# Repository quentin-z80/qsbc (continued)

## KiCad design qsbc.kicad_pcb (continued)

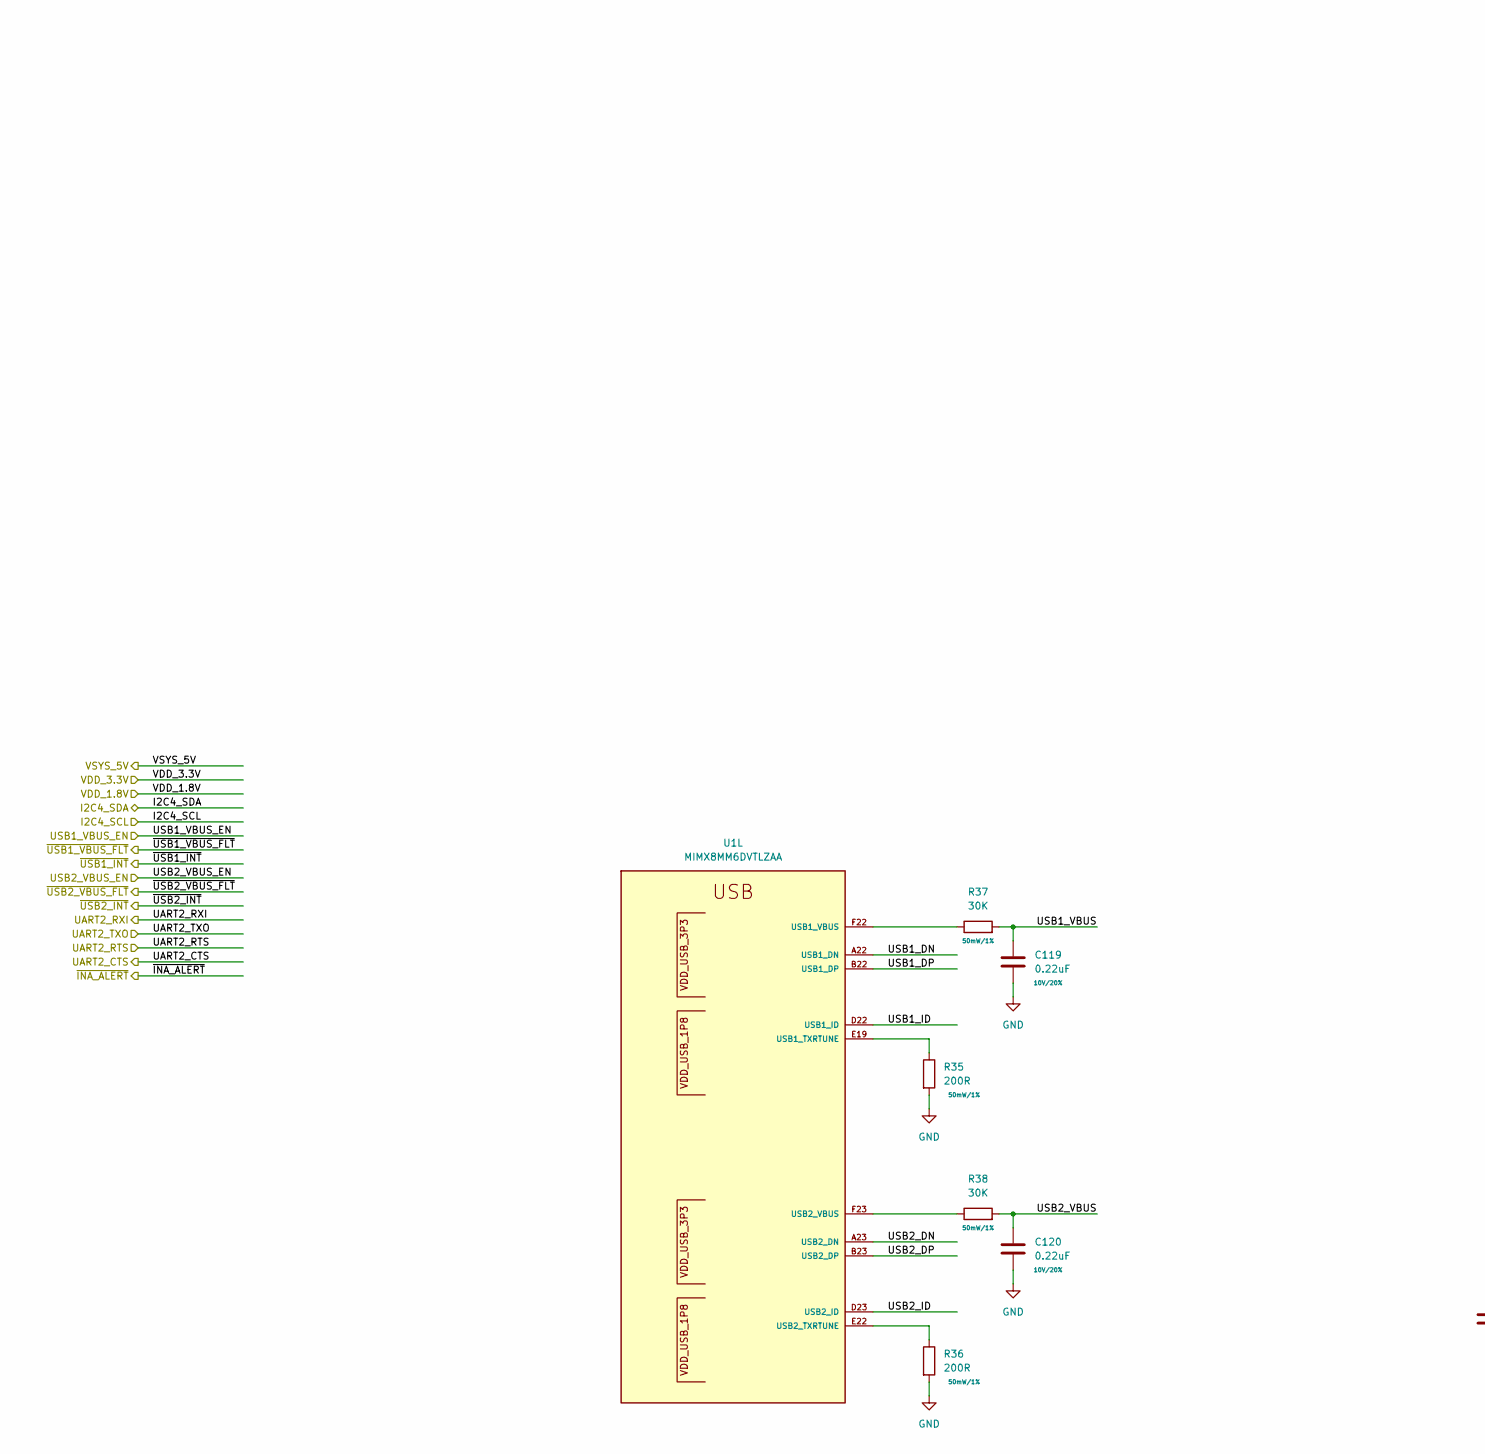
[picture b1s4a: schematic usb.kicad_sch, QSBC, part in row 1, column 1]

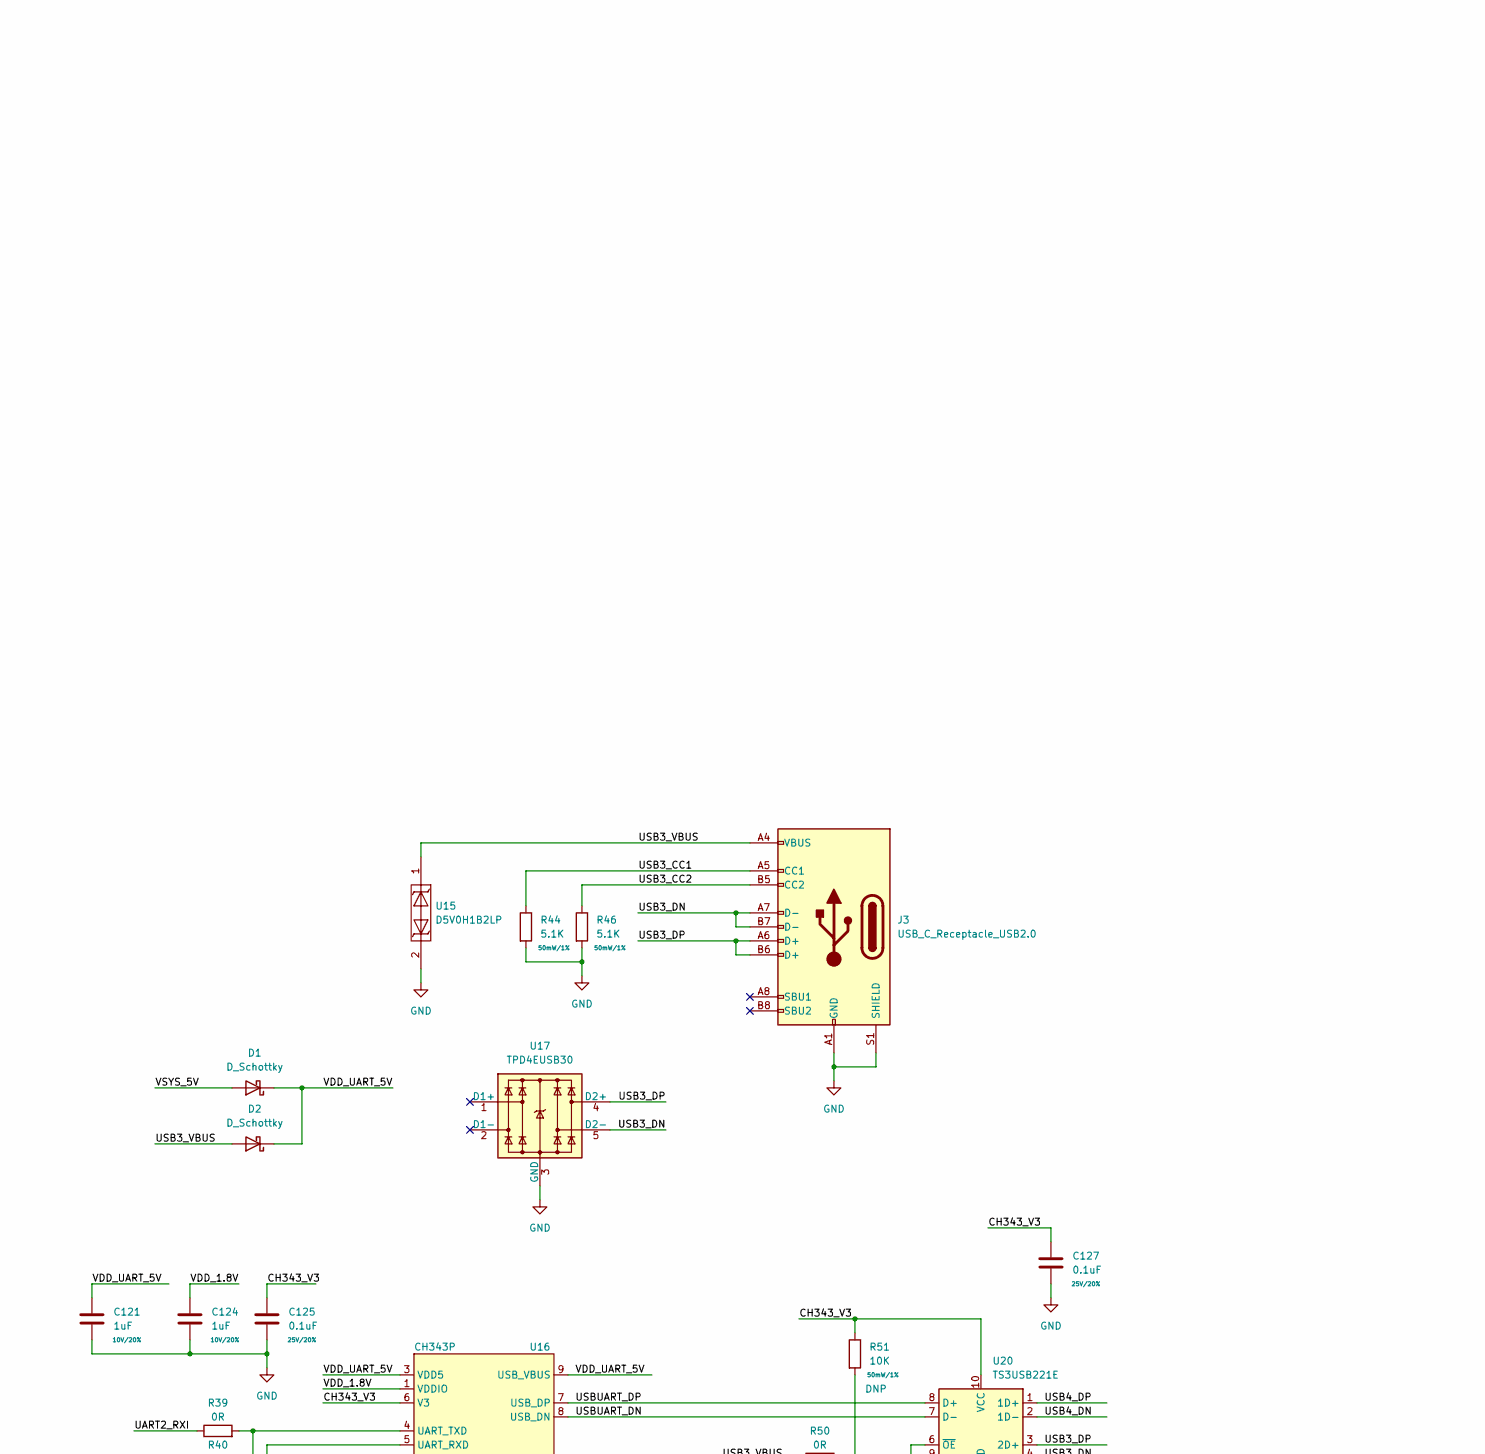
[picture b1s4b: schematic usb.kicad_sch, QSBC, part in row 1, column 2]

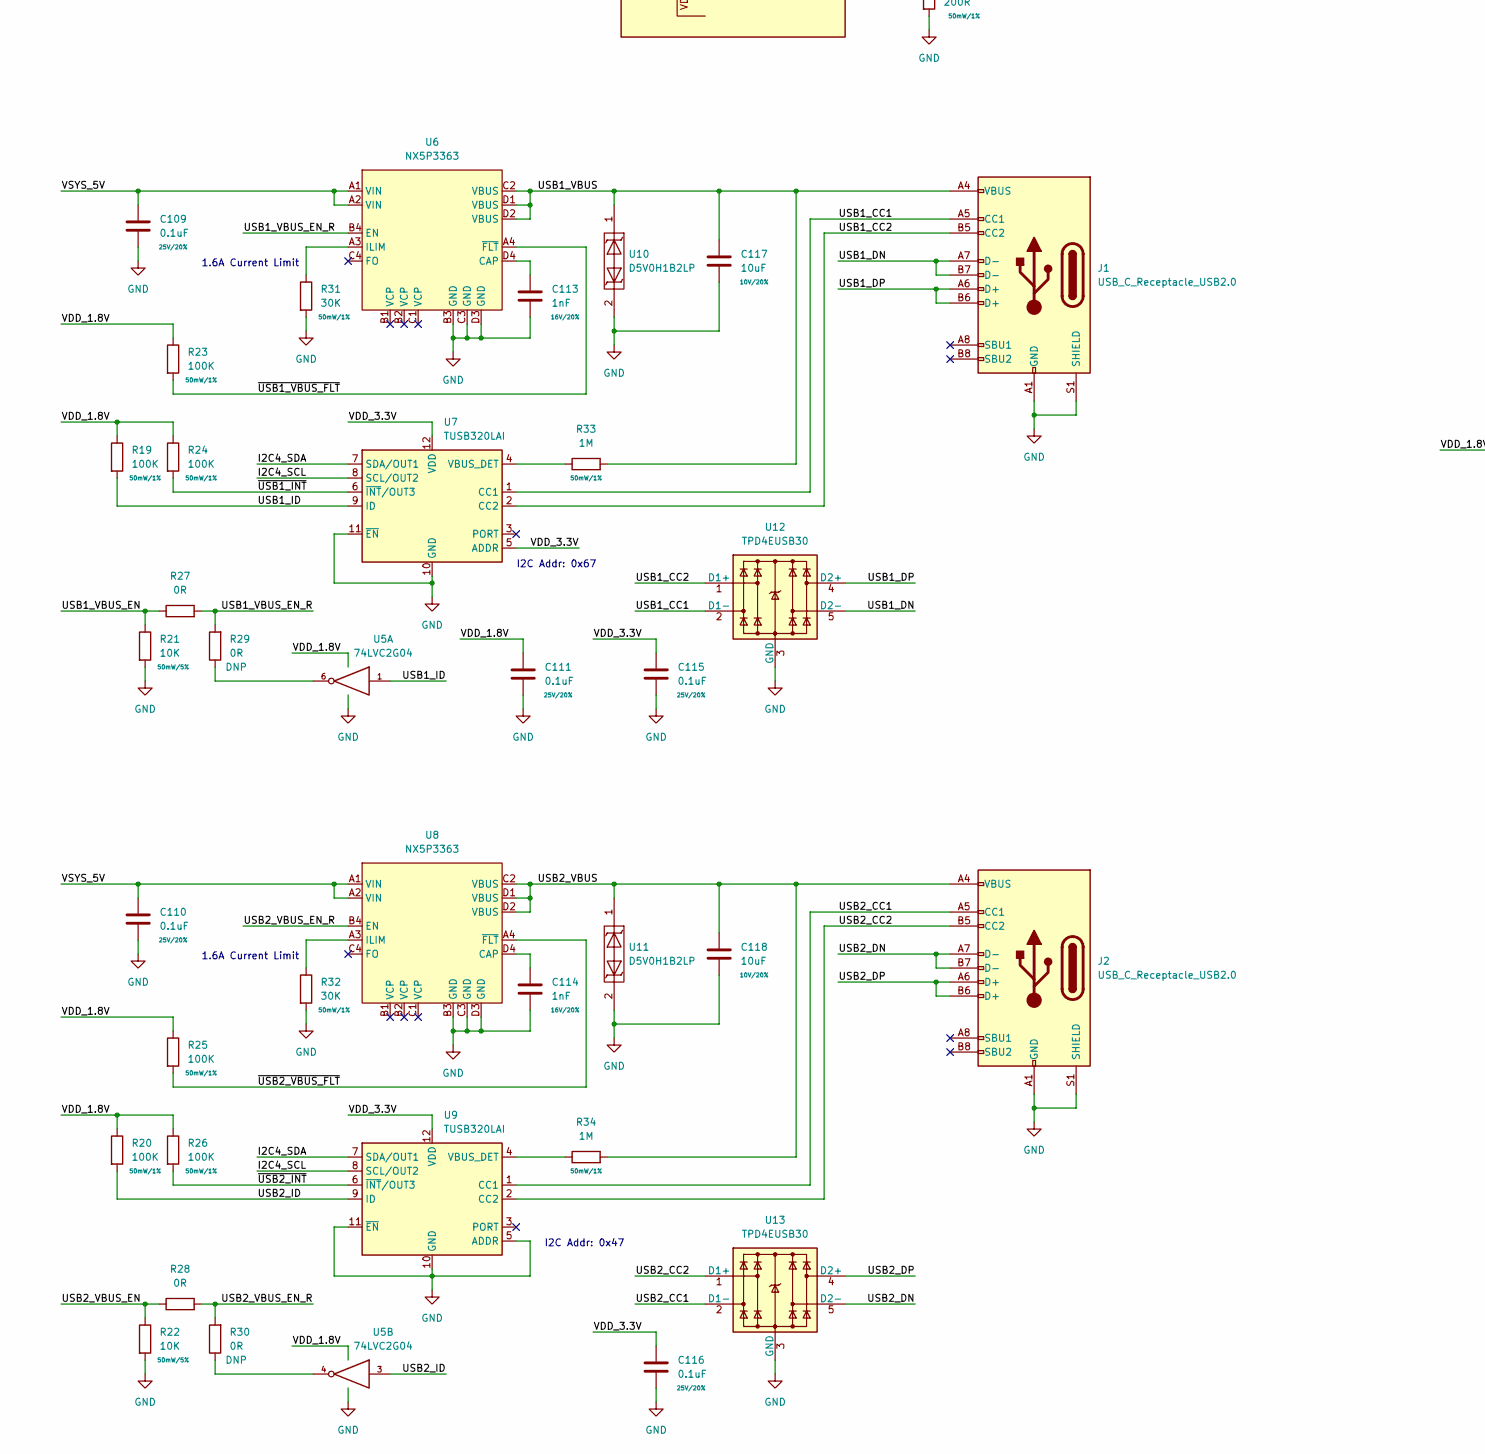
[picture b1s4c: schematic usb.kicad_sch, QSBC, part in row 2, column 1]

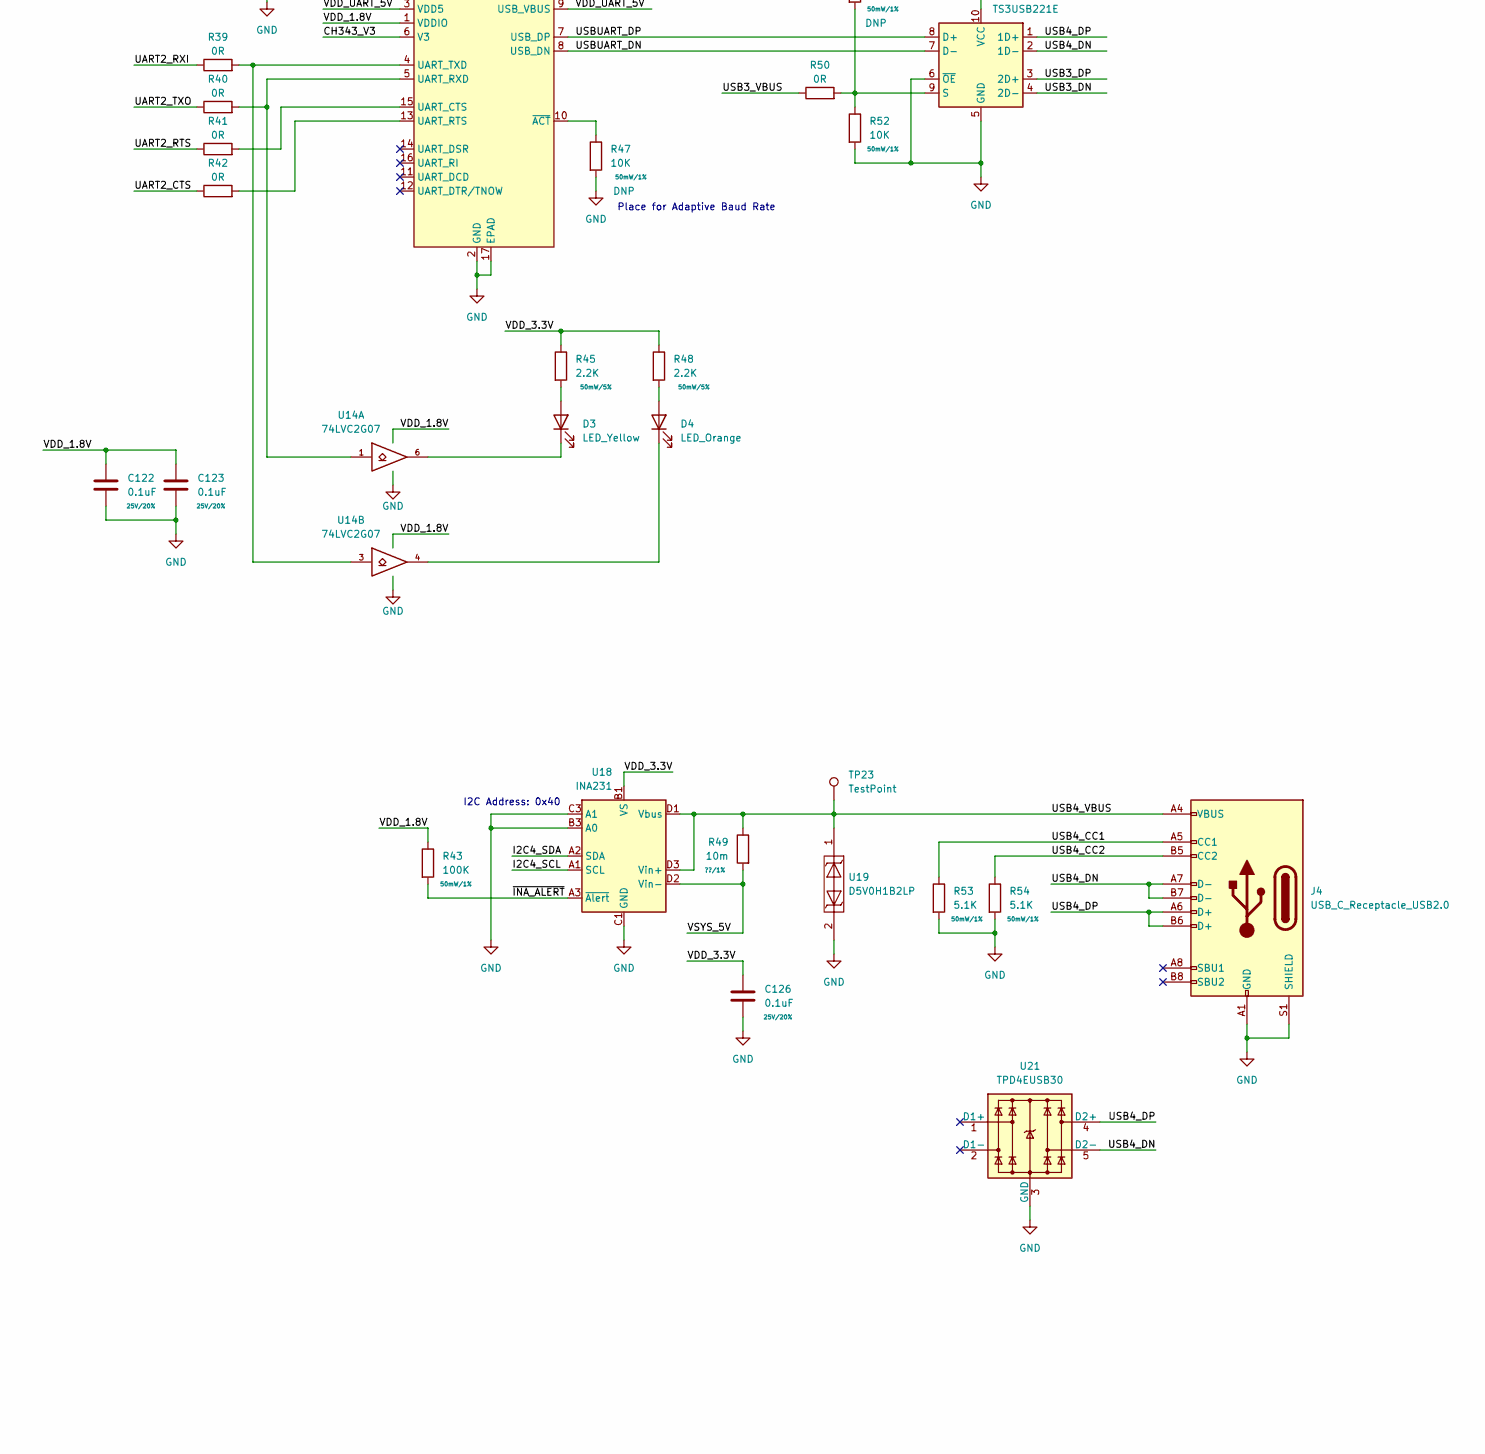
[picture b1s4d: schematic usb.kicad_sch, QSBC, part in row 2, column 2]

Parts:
C109, C110, C111, C115, C116, C122, C123, C125, C126, C127: 0.1uF; C_0402_1005Metric; Rating 25V/20%
C113, C114: 1nF; C_0402_1005Metric; Rating 16V/20%
C117, C118: 10uF; C_0603_1608Metric; Rating 10V/20%
C119, C120: 0.22uF; C_0201_0603Metric; Rating 10V/20%
C121, C124: 1uF; C_0402_1005Metric; Rating 10V/20%
D1, D2: D_Schottky; D_SOD-523
D3: LED_Yellow; LED_0603_1608Metric
D4: LED_Orange; LED_0603_1608Metric
J1, J2, J3, J4: USB_C_Receptacle_USB2.0; USB_C_Receptacle_HRO_TYPE-C-31-M-12
R19, R20, R23, R24, R25, R26, R43: 100K; R_0402_1005Metric; Rating 50mW/1%
R21, R22: 10K; R_0402_1005Metric; Rating 50mW/5%
R27, R28, R29, R30, R39, R40, R41, R42, R50: 0R; R_0402_1005Metric
R31, R32, R37, R38: 30K; R_0201_0603Metric; Rating 50mW/1%
R33, R34: 1M; R_0402_1005Metric; Rating 50mW/1%
R35: 200R; R_0201_0603Metric; Rating 50mW/1%
R36: 200R; R_0402_1005Metric; Rating 50mW/1%
R44, R46, R53, R54: 5.1K; R_0402_1005Metric; Rating 50mW/1%
R45, R48: 2.2K; R_0402_1005Metric; Rating 50mW/5%
R47, R51, R52: 10K; R_0402_1005Metric; Rating 50mW/1%
R49: 10m; R_1206_3216Metric; Rating ??/1%
TP23: TestPoint; TestPoint_Pad_D1.0mm
U1: MIMX8MM6DVTLZAA; SOT1967-1
U5: 74LVC2G04; SOT-886
U6, U8: NX5P3363; WLCSP-16_2.225x2.17mm_P0.5mm
U7, U9: TUSB320LAI; Texas_X2QFN-12_1.6x1.6mm_P0.4mm
U10, U11, U15, U19: D5V0H1B2LP; DFN100X60X45-2N
U12, U13, U17, U21: TPD4EUSB30; USON-10_2.5x1.0mm_P0.5mm
U14: 74LVC2G07; SOT-886
U16: CH343P; QFN-16-1EP_3x3mm_P0.5mm_EP1.45x1.45mm_ThermalVias
U18: INA231; DSBGA-12
U20: TS3USB221E; Texas_R-PUQFN-N10

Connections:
/Peripherals/I2C4_SCL: U7.8 (SCL/OUT2), U9.8 (SCL/OUT2), U18.A1 (SCL); also elsewhere on the board
/Peripherals/I2C4_SDA: U7.7 (SDA/OUT1), U9.7 (SDA/OUT1), U18.A2 (SDA); also elsewhere on the board
/Peripherals/UART2_CTS: R42.1; also elsewhere on the board
/Peripherals/UART2_RTS: R41.1; also elsewhere on the board
/Peripherals/UART2_RXI: R39.1; also elsewhere on the board
/Peripherals/UART2_TXO: R40.1; also elsewhere on the board
/Peripherals/USB1_VBUS_EN: R21.1, R27.1; also elsewhere on the board
/Peripherals/USB2_VBUS_EN: R22.1, R28.1; also elsewhere on the board
/Peripherals/~INA_ALERT: R43.2, U18.A3 (~Alert); also elsewhere on the board
/Peripherals/~USB1_INT: R24.2, U7.6 (~INT/OUT3); also elsewhere on the board
/Peripherals/~USB1_VBUS_FLT: R23.2, U6.A4 (~FLT); also elsewhere on the board
/Peripherals/~USB2_INT: R26.2, U9.6 (~INT/OUT3); also elsewhere on the board
/Peripherals/~USB2_VBUS_FLT: R25.2, U8.A4 (~FLT); also elsewhere on the board
/Power/VSYS_5V: C109.1, C110.1, D1.2 (A), R49.2, U6.A1 (VIN), U6.A2 (VIN), U8.A1 (VIN), U8.A2 (VIN), U18.D2 (Vin-); also elsewhere on the board
/USB/CH343_V3: C125.1, C127.1, R51.1, U16.6 (V3), U20.10 (VCC)
/USB/USB1_CC1: J1.A5 (CC1), U7.1 (CC1), U12.2 (D1-), U12.9
/USB/USB1_CC2: J1.B5 (CC2), U7.2 (CC2), U12.1 (D1+), U12.10
/USB/USB1_DN: J1.A7 (D-), J1.B7 (D-), U1.A22 (USB1_DN), U12.5 (D2-), U12.6
/USB/USB1_DP: J1.A6 (D+), J1.B6 (D+), U1.B22 (USB1_DP), U12.4 (D2+), U12.7
/USB/USB1_ID: R19.2, U1.D22 (USB1_ID), U5.1, U7.9 (ID)
/USB/USB1_VBUS: C117.1, C119.1, J1.A4 (VBUS), J1.A9 (VBUS), J1.B4 (VBUS), J1.B9 (VBUS), R33.2, R37.2, U6.C2 (VBUS), U6.D1 (VBUS), U6.D2 (VBUS), U10.1
/USB/USB1_VBUS_EN_R: R27.2, R29.2, U6.B4 (EN)
/USB/USB2_CC1: J2.A5 (CC1), U9.1 (CC1), U13.2 (D1-), U13.9
/USB/USB2_CC2: J2.B5 (CC2), U9.2 (CC2), U13.1 (D1+), U13.10
/USB/USB2_DN: J2.A7 (D-), J2.B7 (D-), U1.A23 (USB2_DN), U13.5 (D2-), U13.6
/USB/USB2_DP: J2.A6 (D+), J2.B6 (D+), U1.B23 (USB2_DP), U13.4 (D2+), U13.7
/USB/USB2_ID: R20.2, U1.D23 (USB2_ID), U5.3, U9.9 (ID)
/USB/USB2_VBUS: C118.1, C120.1, J2.A4 (VBUS), J2.A9 (VBUS), J2.B4 (VBUS), J2.B9 (VBUS), R34.2, R38.2, U8.C2 (VBUS), U8.D1 (VBUS), U8.D2 (VBUS), U11.1
/USB/USB2_VBUS_EN_R: R28.2, R30.2, U8.B4 (EN)
/USB/USB3_CC1: J3.A5 (CC1), R44.1
/USB/USB3_CC2: J3.B5 (CC2), R46.1
/USB/USB3_DN: J3.A7 (D-), J3.B7 (D-), U17.5 (D2-), U17.6, U20.4 (2D-)
/USB/USB3_DP: J3.A6 (D+), J3.B6 (D+), U17.4 (D2+), U17.7, U20.3 (2D+)
/USB/USB3_VBUS: D2.2 (A), J3.A4 (VBUS), J3.A9 (VBUS), J3.B4 (VBUS), J3.B9 (VBUS), R50.1, U15.1
/USB/USB4_CC1: J4.A5 (CC1), R53.1
/USB/USB4_CC2: J4.B5 (CC2), R54.1
/USB/USB4_DN: J4.A7 (D-), J4.B7 (D-), U20.2 (1D-), U21.5 (D2-), U21.6
/USB/USB4_DP: J4.A6 (D+), J4.B6 (D+), U20.1 (1D+), U21.4 (D2+), U21.7
/USB/USB4_VBUS: J4.A4 (VBUS), J4.A9 (VBUS), J4.B4 (VBUS), J4.B9 (VBUS), R49.1, TP23.1, U18.D1 (Vbus), U18.D3 (Vin+), U19.1
/USB/USBUART_DN: U16.8 (USB_DN), U20.7 (D-)
/USB/USBUART_DP: U16.7 (USB_DP), U20.8 (D+)
/USB/VDD_UART_5V: C121.1, D1.1 (K), D2.1 (K), U16.3 (VDD5), U16.9 (USB_VBUS)
GND: C109.2, C110.2, C111.2, C113.2, C114.2, C115.2, C116.2, C117.2, C118.2, C119.2, C120.2, C121.2, C122.2, C123.2, C124.2, C125.2, C126.2, C127.2, J1.A1 (GND), J1.A12 (GND), J1.B1 (GND), J1.B12 (GND), J1.S1 (SHIELD), J2.A1 (GND), J2.A12 (GND), J2.B1 (GND), J2.B12 (GND), J2.S1 (SHIELD), J3.A1 (GND), J3.A12 (GND), J3.B1 (GND), J3.B12 (GND), J3.S1 (SHIELD), J4.A1 (GND), J4.A12 (GND), J4.B1 (GND), J4.B12 (GND), J4.S1 (SHIELD), R21.2, R22.2, R31.2, R32.2, R35.2, R36.2, R44.2, R46.2, R47.2, R52.2, R53.2, R54.2, U5.2 (GND), U6.B3 (GND), U6.C3 (GND), U6.D3 (GND), U7.10 (GND), U7.11 (~EN), U8.B3 (GND), U8.C3 (GND), U8.D3 (GND), U9.5 (ADDR), U9.10 (GND), U9.11 (~EN), U10.2, U11.2, U12.3 (GND), U12.8 (GND), U13.3 (GND), U13.8 (GND), U14.2 (GND), U15.2, U16.2 (GND), U16.17 (EPAD), U17.3 (GND), U17.8 (GND), U18.B3 (A0), U18.C1 (GND), U18.C3 (A1), U19.2, U20.5 (GND), U20.6 (~OE), U21.3 (GND), U21.8 (GND); also elsewhere on the board
unnamed: C113.1, U6.D4 (CAP)
unnamed: C114.1, U8.D4 (CAP)
unnamed: D3.1 (K), U14.6
unnamed: D3.2 (A), R45.2
unnamed: D4.1 (K), U14.4
unnamed: D4.2 (A), R48.2
unnamed: R29.1, U5.6
unnamed: R30.1, U5.4
unnamed: R31.1, U6.A3 (ILIM)
unnamed: R32.1, U8.A3 (ILIM)
unnamed: R33.1, U7.4 (VBUS_DET)
unnamed: R34.1, U9.4 (VBUS_DET)
unnamed: R35.1, U1.E19 (USB1_TXRTUNE)
unnamed: R36.1, U1.E22 (USB2_TXRTUNE)
unnamed: R37.1, U1.F22 (USB1_VBUS)
unnamed: R38.1, U1.F23 (USB2_VBUS)
unnamed: R39.2, U14.3, U16.4 (UART_TXD)
unnamed: R40.2, U14.1, U16.5 (UART_RXD)
unnamed: R41.2, U16.15 (UART_CTS)
unnamed: R42.2, U16.13 (UART_RTS)
unnamed: R47.1, U16.10 (~ACT)
unnamed: R50.2, R51.2, R52.1, U20.9 (S)
VDD_1.8V: C111.1, C122.1, C123.1, C124.1, R19.1, R20.1, R23.1, R24.1, R25.1, R26.1, R43.1, U5.5 (VCC), U14.5 (VCC), U16.1 (VDDIO); also elsewhere on the board
VDD_3.3V: C115.1, C116.1, C126.1, R45.1, R48.1, U7.5 (ADDR), U7.12 (VDD), U9.12 (VDD), U18.B1 (VS); also elsewhere on the board

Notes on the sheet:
Place for Adaptive Baud Rate
I2C Addr: 0x67
I2C Addr: 0x47
1.6A Current Limit
I2C Address: 0x40

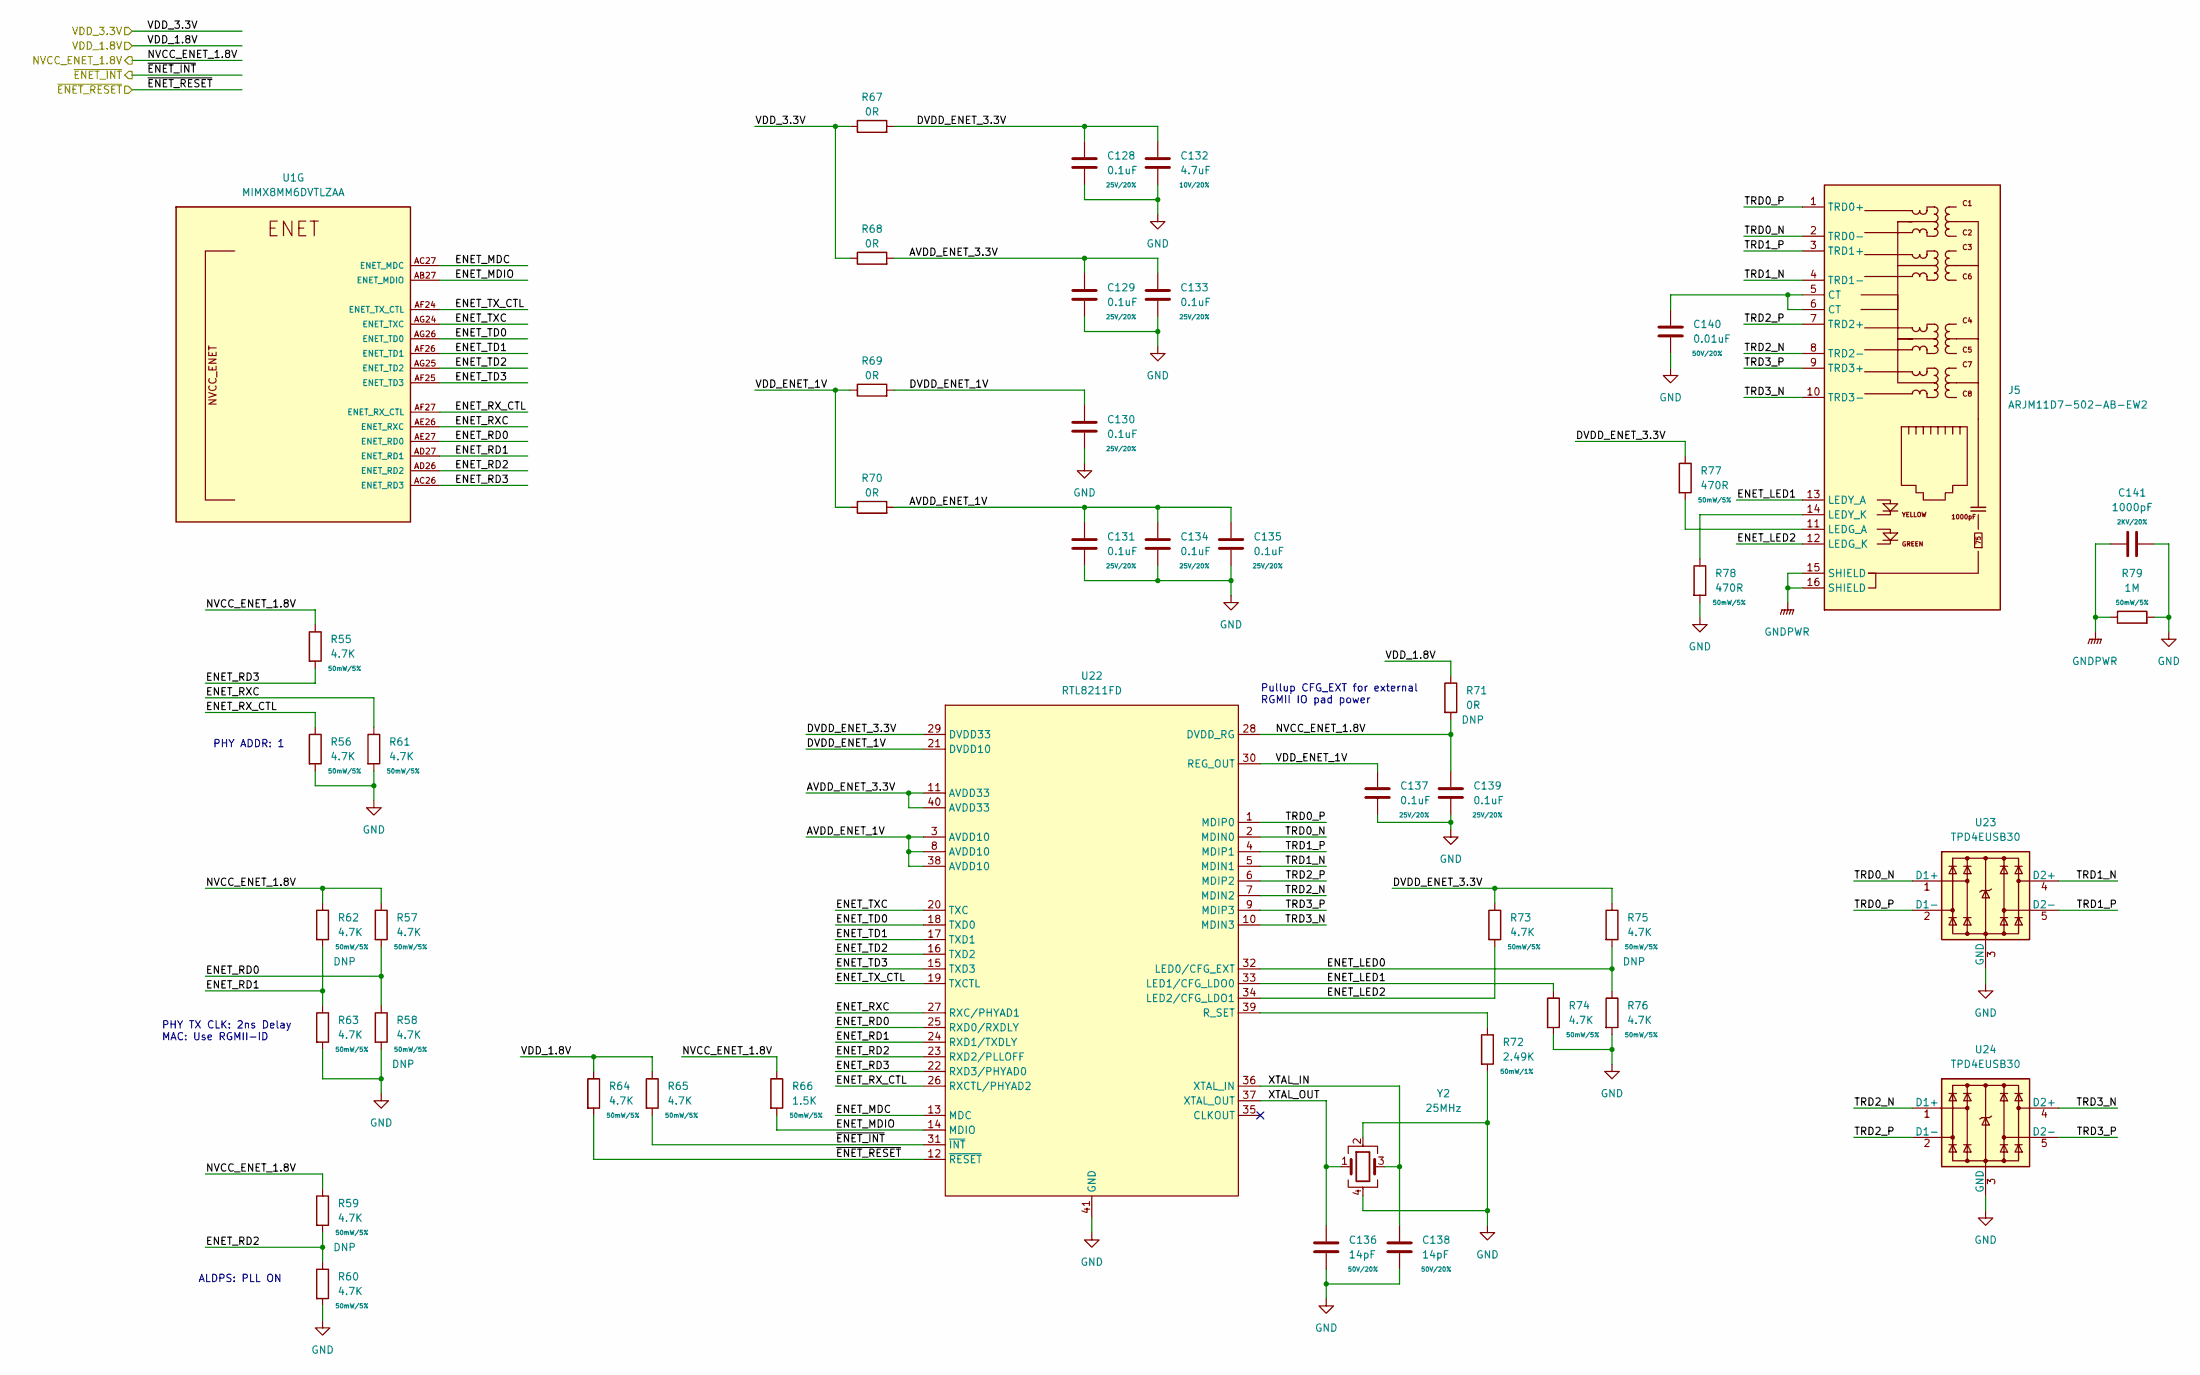
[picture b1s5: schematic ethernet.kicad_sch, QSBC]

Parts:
C128, C129, C130, C131, C133, C134, C135, C137, C139: 0.1uF; C_0402_1005Metric; Rating 25V/20%
C132: 4.7uF; C_0402_1005Metric; Rating 10V/20%
C136, C138: 14pF; C_0402_1005Metric; Rating 50V/20%
C140: 0.01uF; C_0603_1608Metric; Rating 50V/20%
C141: 1000pF; C_1210_3225Metric; Rating 2KV/20%
J5: ARJM11D7-502-AB-EW2
R55, R56, R57, R58, R59, R60, R61, R62, R63, R64, R65, R73, R74, R75, R76: 4.7K; R_0402_1005Metric; Rating 50mW/5%
R66: 1.5K; R_0402_1005Metric; Rating 50mW/5%
R67, R68, R69, R70, R71: 0R; R_0402_1005Metric
R72: 2.49K; R_0402_1005Metric; Rating 50mW/1%
R77, R78: 470R; R_0402_1005Metric; Rating 50mW/5%
R79: 1M; R_1206_3216Metric; Rating 50mW/5%
U1: MIMX8MM6DVTLZAA; SOT1967-1
U22: RTL8211FD; QFN-40-1EP_5x5mm_P0.4mm_EP3.6x3.6mm_ThermalVias
U23, U24: TPD4EUSB30; USON-10_2.5x1.0mm_P0.5mm
Y2: 25MHz; Crystal_SMD_3225-4Pin_3.2x2.5mm; MPN ECS-250-10-33B-CWN-TR

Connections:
/Ethernet/AVDD_ENET_1V: C131.1, C134.1, C135.1, R70.2, U22.3 (AVDD10), U22.8 (AVDD10), U22.38 (AVDD10)
/Ethernet/AVDD_ENET_3.3V: C129.1, C133.1, R68.2, U22.11 (AVDD33), U22.40 (AVDD33)
/Ethernet/DVDD_ENET_1V: C130.1, R69.2, U22.21 (DVDD10)
/Ethernet/DVDD_ENET_3.3V: C128.1, C132.1, R67.2, R73.1, R75.1, R77.1, U22.29 (DVDD33)
/Ethernet/ENET_LED0: R75.2, R76.1, U22.32 (LED0/CFG_EXT)
/Ethernet/ENET_LED1: J5.13 (LEDY_A), R74.1, U22.33 (LED1/CFG_LDO0)
/Ethernet/ENET_LED2: J5.12 (LEDG_K), R73.2, U22.34 (LED2/CFG_LDO1)
/Ethernet/ENET_MDC: U1.AC27 (ENET_MDC), U22.13 (MDC)
/Ethernet/ENET_MDIO: R66.2, U1.AB27 (ENET_MDIO), U22.14 (MDIO)
/Ethernet/ENET_RD0: R57.2, R58.1, U1.AE27 (ENET_RD0), U22.25 (RXD0/RXDLY)
/Ethernet/ENET_RD1: R62.2, R63.1, U1.AD27 (ENET_RD1), U22.24 (RXD1/TXDLY)
/Ethernet/ENET_RD2: R59.2, R60.1, U1.AD26 (ENET_RD2), U22.23 (RXD2/PLLOFF)
/Ethernet/ENET_RD3: R55.2, U1.AC26 (ENET_RD3), U22.22 (RXD3/PHYAD0)
/Ethernet/ENET_RXC: R61.1, U1.AE26 (ENET_RXC), U22.27 (RXC/PHYAD1)
/Ethernet/ENET_RX_CTL: R56.1, U1.AF27 (ENET_RX_CTL), U22.26 (RXCTL/PHYAD2)
/Ethernet/ENET_TD0: U1.AG26 (ENET_TD0), U22.18 (TXD0)
/Ethernet/ENET_TD1: U1.AF26 (ENET_TD1), U22.17 (TXD1)
/Ethernet/ENET_TD2: U1.AG25 (ENET_TD2), U22.16 (TXD2)
/Ethernet/ENET_TD3: U1.AF25 (ENET_TD3), U22.15 (TXD3)
/Ethernet/ENET_TXC: U1.AG24 (ENET_TXC), U22.20 (TXC)
/Ethernet/ENET_TX_CTL: U1.AF24 (ENET_TX_CTL), U22.19 (TXCTL)
/Ethernet/NVCC_ENET_1.8V: C139.1, R55.1, R57.1, R59.1, R62.1, R66.1, R71.2, U22.28 (DVDD_RG); also elsewhere on the board
/Ethernet/TRD0_N: J5.2 (TRD0-), U22.2 (MDIN0), U23.1 (D1+), U23.10
/Ethernet/TRD0_P: J5.1 (TRD0+), U22.1 (MDIP0), U23.2 (D1-), U23.9
/Ethernet/TRD1_N: J5.4 (TRD1-), U22.5 (MDIN1), U23.4 (D2+), U23.7
/Ethernet/TRD1_P: J5.3 (TRD1+), U22.4 (MDIP1), U23.5 (D2-), U23.6
/Ethernet/TRD2_N: J5.8 (TRD2-), U22.7 (MDIN2), U24.1 (D1+), U24.10
/Ethernet/TRD2_P: J5.7 (TRD2+), U22.6 (MDIP2), U24.2 (D1-), U24.9
/Ethernet/TRD3_N: J5.10 (TRD3-), U22.10 (MDIN3), U24.4 (D2+), U24.7
/Ethernet/TRD3_P: J5.9 (TRD3+), U22.9 (MDIP3), U24.5 (D2-), U24.6
/Ethernet/VDD_ENET_1V: C137.1, R69.1, R70.1, U22.30 (REG_OUT)
/Ethernet/XTAL_IN: C138.1, U22.36 (XTAL_IN), Y2.3
/Ethernet/XTAL_OUT: C136.1, U22.37 (XTAL_OUT), Y2.1
/Ethernet/~ENET_INT: R65.2, U22.31 (~INT); also elsewhere on the board
/Ethernet/~ENET_RESET: R64.2, U22.12 (~RESET); also elsewhere on the board
GND: C128.2, C129.2, C130.2, C131.2, C132.2, C133.2, C134.2, C135.2, C136.2, C137.2, C138.2, C139.2, C140.2, C141.2, R56.2, R58.2, R60.2, R61.2, R63.2, R72.2, R74.2, R76.2, R78.2, R79.2, U22.41 (GND), U23.3 (GND), U23.8 (GND), U24.3 (GND), U24.8 (GND), Y2.2, Y2.4; also elsewhere on the board
GNDPWR: C141.1, J5.15 (SHIELD), J5.16 (SHIELD), R79.1
unnamed: C140.1, J5.5 (CT), J5.6 (CT)
unnamed: J5.11 (LEDG_A), R77.2
unnamed: J5.14 (LEDY_K), R78.1
unnamed: R72.1, U22.39 (R_SET)
VDD_1.8V: R64.1, R65.1, R71.1; also elsewhere on the board
VDD_3.3V: R67.1, R68.1; also elsewhere on the board

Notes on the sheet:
ALDPS: PLL ON
PHY ADDR: 1
Pullup CFG_EXT for external RGMII IO pad power
PHY TX CLK: 2ns Delay MAC: Use RGMII-ID

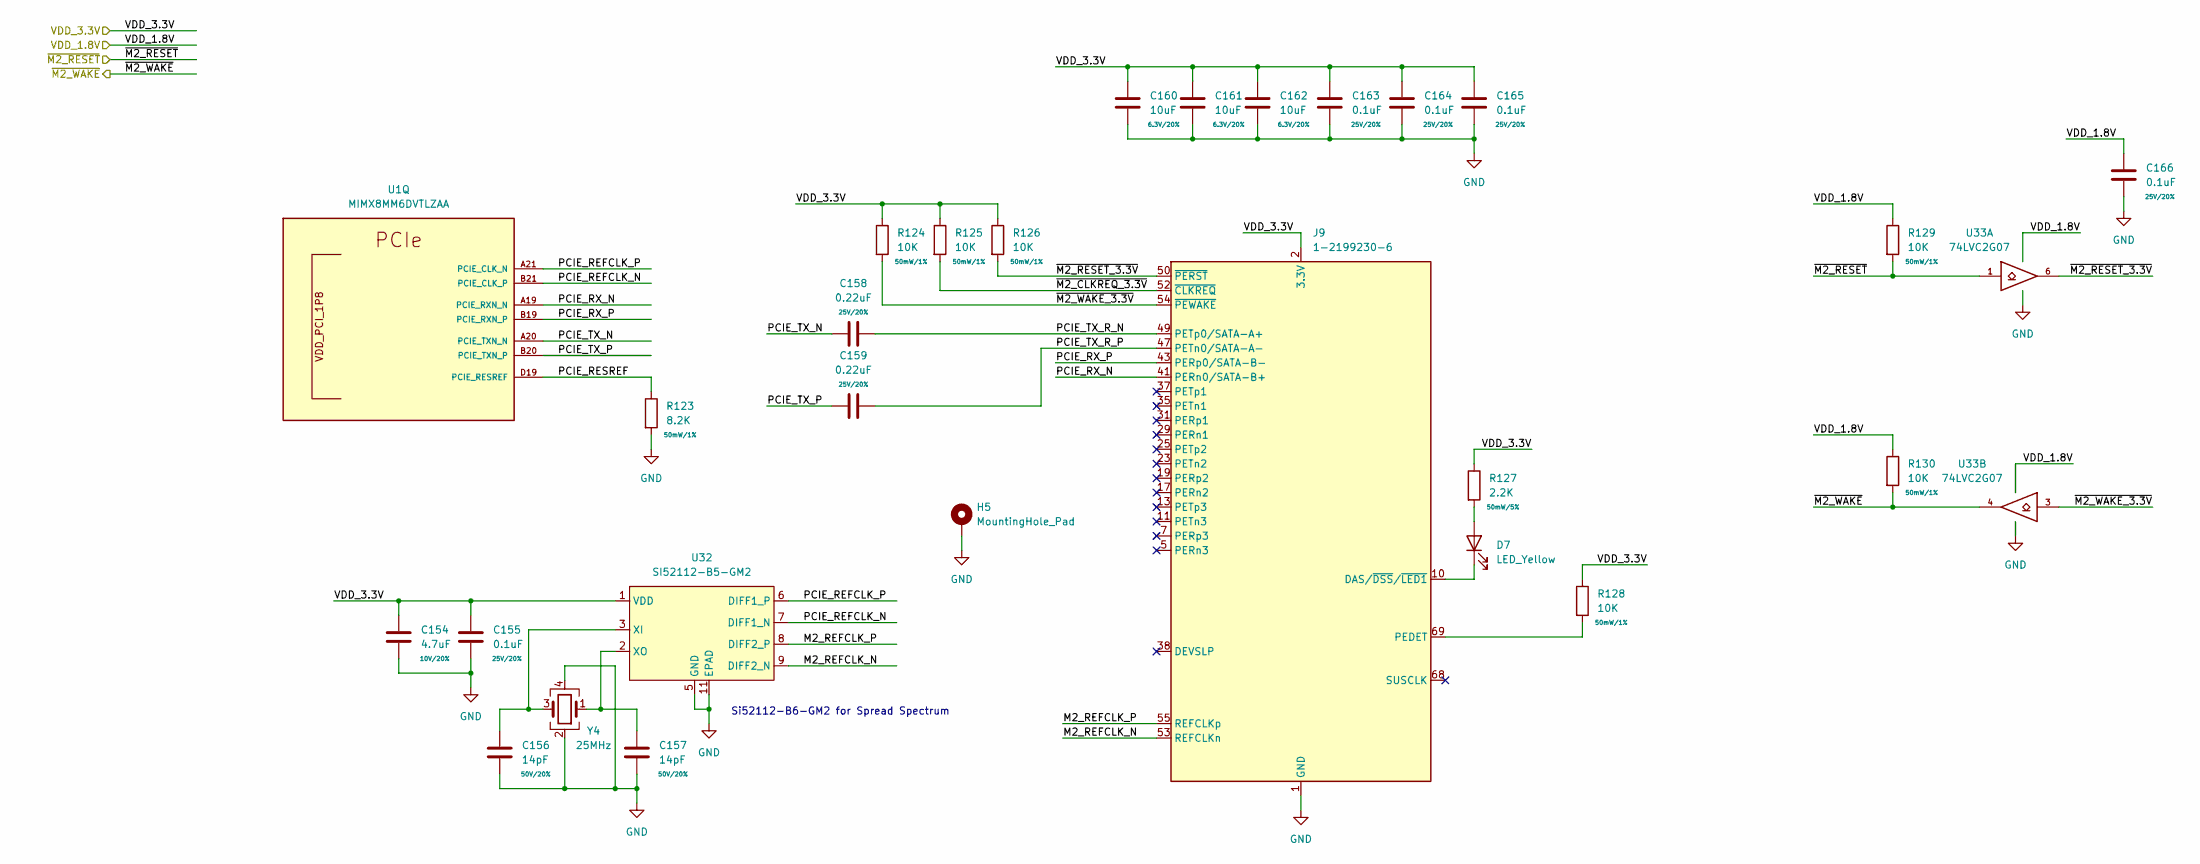
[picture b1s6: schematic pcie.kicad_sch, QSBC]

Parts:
C154: 4.7uF; C_0402_1005Metric; Rating 10V/20%
C155, C163, C164, C165, C166: 0.1uF; C_0402_1005Metric; Rating 25V/20%
C156, C157: 14pF; C_0402_1005Metric; Rating 50V/20%
C158, C159: 0.22uF; C_0201_0603Metric; Rating 25V/20%
C160, C161, C162: 10uF; C_0402_1005Metric; Rating 6.3V/20%
D7: LED_Yellow; LED_0603_1608Metric
H5: MountingHole_Pad; Mounting_Wuerth_WA-SMSI-M3_H2.5mm_9774025360
J9: 1-2199230-6
R123: 8.2K; R_0402_1005Metric; Rating 50mW/1%
R124, R125, R126, R128, R129, R130: 10K; R_0402_1005Metric; Rating 50mW/1%
R127: 2.2K; R_0402_1005Metric; Rating 50mW/5%
U1: MIMX8MM6DVTLZAA; SOT1967-1
U32: SI52112-B5-GM2; DFN-10-1EP_3x3mm_P0.5mm_EP1.55x2.48mm
U33: 74LVC2G07; SOT-886
Y4: 25MHz; Crystal_SMD_3225-4Pin_3.2x2.5mm; MPN ECS-250-10-33B-CWN-TR

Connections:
/PCIe/M2_REFCLK_N: J9.53 (REFCLKn), U32.9 (DIFF2_N)
/PCIe/M2_REFCLK_P: J9.55 (REFCLKp), U32.8 (DIFF2_P)
/PCIe/PCIE_REFCLK_N: U1.B21 (PCIE_CLK_P), U32.7 (DIFF1_N)
/PCIe/PCIE_REFCLK_P: U1.A21 (PCIE_CLK_N), U32.6 (DIFF1_P)
/PCIe/PCIE_RESREF: R123.1, U1.D19 (PCIE_RESREF)
/PCIe/PCIE_RX_N: J9.41 (PERn0/SATA-B+), U1.A19 (PCIE_RXN_N)
/PCIe/PCIE_RX_P: J9.43 (PERp0/SATA-B-), U1.B19 (PCIE_RXN_P)
/PCIe/PCIE_TX_N: C158.1, U1.A20 (PCIE_TXN_N)
/PCIe/PCIE_TX_P: C159.1, U1.B20 (PCIE_TXN_P)
/PCIe/PCIE_TX_R_N: C158.2, J9.49 (PETp0/SATA-A+)
/PCIe/PCIE_TX_R_P: C159.2, J9.47 (PETn0/SATA-A-)
/PCIe/~M2_CLKREQ_3.3V: J9.52 (~CLKREQ), R125.2
/PCIe/~M2_RESET_3.3V: J9.50 (~PERST), R126.2, U33.6
/PCIe/~M2_RESET: R129.2, U33.1; also elsewhere on the board
/PCIe/~M2_WAKE_3.3V: J9.54 (~PEWAKE), R124.2, U33.3
/PCIe/~M2_WAKE: R130.2, U33.4; also elsewhere on the board
GND: C154.2, C155.2, C156.2, C157.2, C160.2, C161.2, C162.2, C163.2, C164.2, C165.2, C166.2, H5.1, J9.1 (GND), J9.3 (GND), J9.9 (GND), J9.15 (GND), J9.21 (GND), J9.27 (GND), J9.33 (GND), J9.39 (GND), J9.45 (GND), J9.51 (GND), J9.57 (GND), J9.71 (GND), J9.73 (GND), J9.75 (GND), R123.2, U32.4 (GND), U32.5 (GND), U32.11 (EPAD), U33.2 (GND), Y4.2, Y4.4; also elsewhere on the board
unnamed: C156.1, U32.3 (XI), Y4.3
unnamed: C157.1, U32.2 (XO), Y4.1
unnamed: D7.1 (K), J9.10 (DAS/~DSS/~LED1)
unnamed: D7.2 (A), R127.2
unnamed: J9.69 (PEDET), R128.2
VDD_1.8V: C166.1, R129.1, R130.1, U33.5 (VCC); also elsewhere on the board
VDD_3.3V: C154.1, C155.1, C160.1, C161.1, C162.1, C163.1, C164.1, C165.1, J9.2 (3.3V), J9.4 (3.3V), J9.12 (3.3V), J9.14 (3.3V), J9.16 (3.3V), J9.18 (3.3V), J9.70 (3.3V), J9.72 (3.3V), J9.74 (3.3V), R124.1, R125.1, R126.1, R127.1, R128.1, U32.1 (VDD), U32.10 (VDD); also elsewhere on the board

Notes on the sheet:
Si52112-B6-GM2 for Spread Spectrum
